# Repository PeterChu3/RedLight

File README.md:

# RedLight

## Story

I ride around Atlanta on the electric mini bike pictured above. However, there is no lighting in the rear. Which according to car drivers can be hard to see at night. Rather than buy a cheap small internal battery powered red light from Amazon. I decided to make a overpowered blinking red light powered by the bike's battery to make sure everyone knows I exist on the road. I don't want to be hit by another car.

## Explanation

Uses a 555 timer and a n-channel mosfet to turn on/off LEDs.

The 555 timer is set to a 1-1.5 Hz signal astable square wave providing a steady rear LED.

The input voltage is 12v

rev# marks an existing PCB that has been ordered and purchased. After a rev# is submitted and purchased that revision will not be edited anymore and the next revision will be started. The current revision is rev1

#### Important links for design

LEDs
https://www.mouser.com/ProductDetail/941-XPEBRDL1R250601

LED datasheet
https://www.mouser.com/datasheet/2/723/XLampXPE2-2327163.pdf

LED Eye Safety
https://cree-led.com/media/documents/XLamp_EyeSafety.pdf

LED PCB Thermals
https://cree-led.com/media/documents/XLamp_PCB_Thermal.pdf

## Schematic and Board layout

Schematic view

Layout view

Board view

Functional test

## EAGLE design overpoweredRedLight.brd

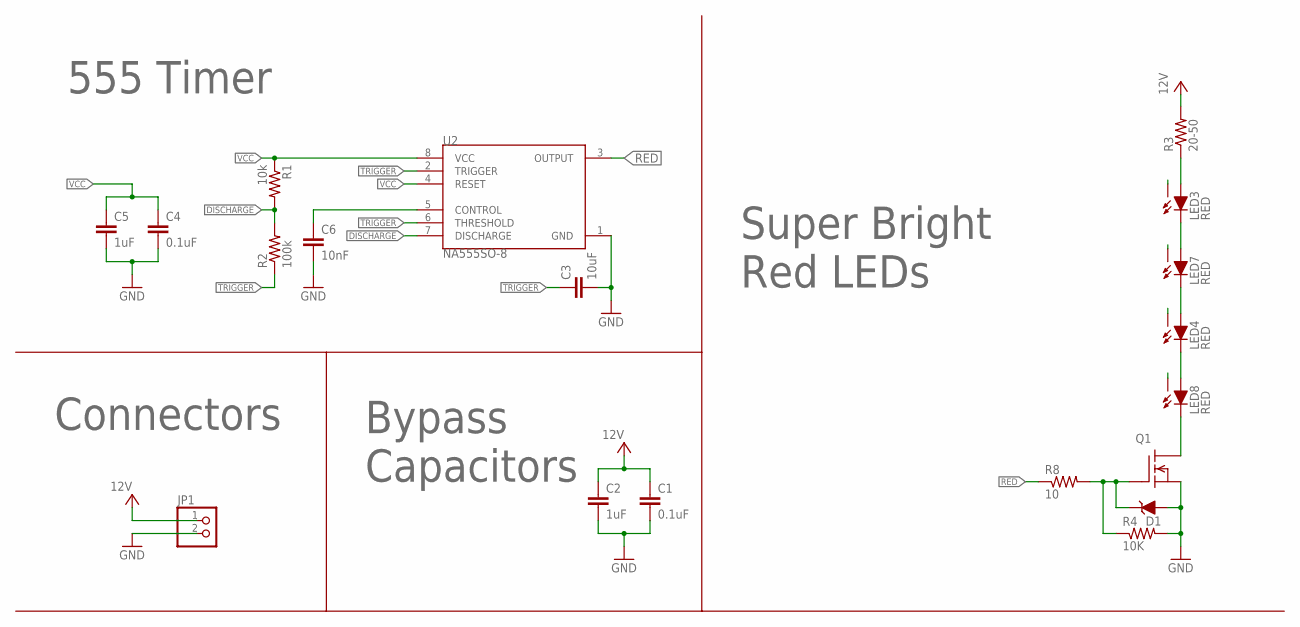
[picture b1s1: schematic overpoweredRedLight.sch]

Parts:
C1, C4: 0.1uF; 0603-CAP; TOLERANCE 5%; VOLTAGE 25V
C2, C5: 1uF; 0603-CAP; TOLERANCE 5%; VOLTAGE 25V
C3: 10uF; 0603-CAP; TOLERANCE 5%; VOLTAGE 25V
C6: 10nF; 0603-CAP; TOLERANCE 5%; VOLTAGE 25V
D1: MMBZ5246BLT1G; SOT23
JP1: PINHD-1X2; 1X02
LED3, LED4, LED7, LED8: RED; XP-E2
Q1: DMG3406LSOT; SOT23
R1: 10k; 0603-RES; TOLERANCE 1%
R2: 100k; 0603-RES; TOLERANCE 1%
R3: 20-50; 1W-0.6
R4: 10K; 0603-RES; TOLERANCE 1%
R8: 10; 0603-RES; TOLERANCE 1%
U2: NA555SO-8; SOIC-08

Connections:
DISCHARGE: R1.2, R2.2, U2.7 (DISCHARGE)
GND: C1.2, C2.2, C3.2, C4.2, C5.2, C6.2, D1.1 (A), JP1.2, Q1.2 (S), R4.2, U2.1 (GND)
unnamed: D1.3 (C), Q1.1 (G), R4.1, R8.2
unnamed: LED8.C, Q1.3 (D)
unnamed: LED3.A, R3.1
unnamed: C6.1, U2.5 (CONTROL)
unnamed: LED3.C, LED7.A
unnamed: LED4.A, LED7.C
unnamed: LED4.C, LED8.A
RED: R8.1, U2.3 (OUTPUT)
THERM1: LED4.X, LED8.X
THERM2: LED3.X, LED7.X
TRIGGER: C3.1, R2.1, U2.2 (TRIGGER), U2.6 (THRESHOLD)
VCC: C1.1, C2.1, C4.1, C5.1, JP1.1, R1.1, R3.2, U2.4 (RESET), U2.8 (VCC)

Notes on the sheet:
555 Timer
Super Bright Red LEDs
Connectors
Bypass Capacitors

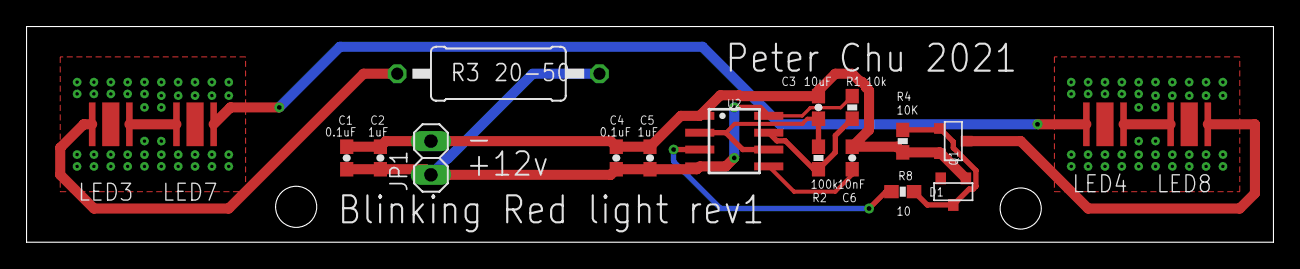
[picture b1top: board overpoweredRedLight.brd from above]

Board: 2 copper layers, 94.0 x 16.3 mm, 19 parts (0 on the bottom side), 14 nets.

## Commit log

2021-11-10 Blinking Red light revision 1
2021-11-10 Added images
2021-11-10 Added images and updated readme
2021-11-10 Updated board image
2021-11-10 Updated gif and readme
2021-11-10 Edit silkscreen
2021-11-10 Final gerber files before submition to JLC
2022-03-08 Added functional circuit gif.
